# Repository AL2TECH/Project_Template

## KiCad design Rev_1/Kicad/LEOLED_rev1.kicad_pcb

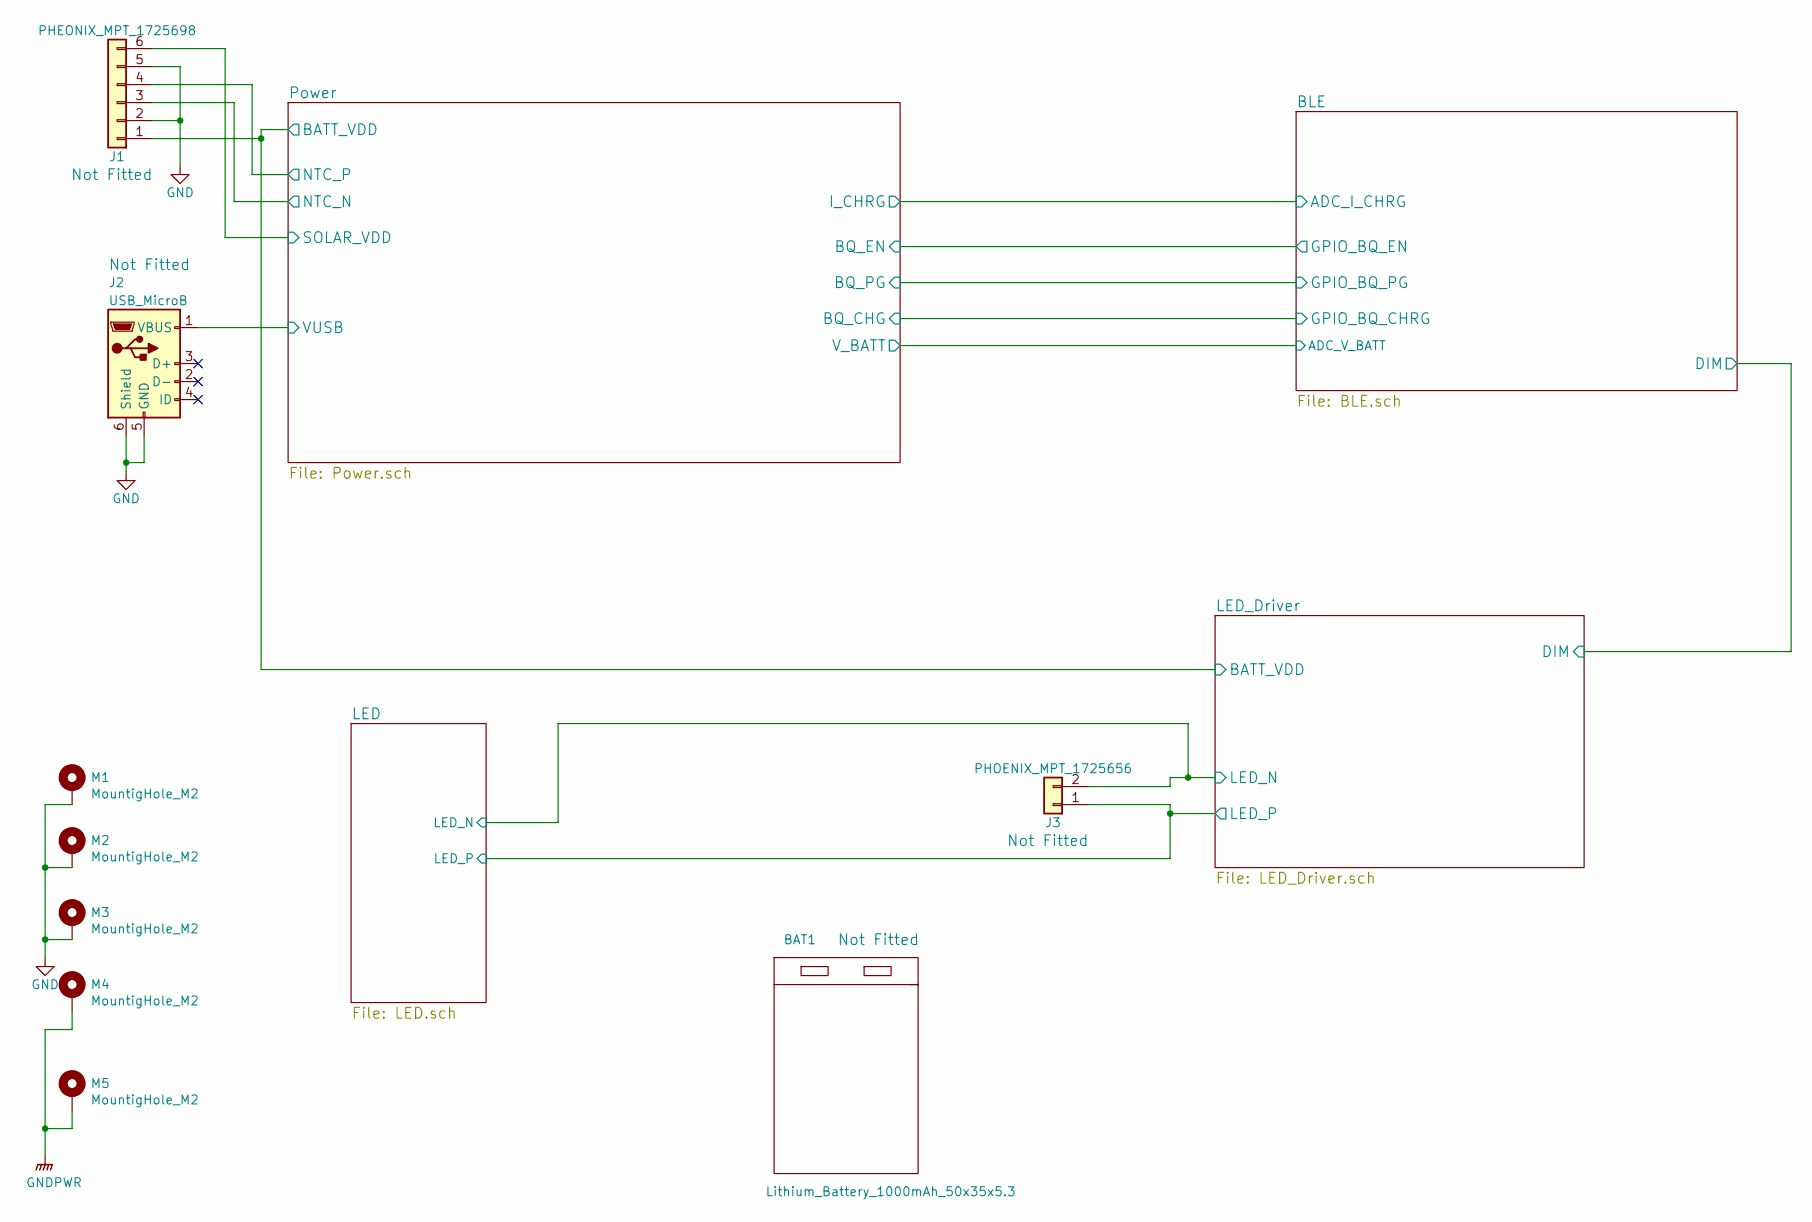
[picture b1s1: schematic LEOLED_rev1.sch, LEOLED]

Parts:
BAT1: Lithium_Battery_1000mAh_50x35x5.3; Lithium_battery_50x30x5.3; Rating 1000mAh, 3.7V; Tolerance NA; Manufacturer PN 523450
J1: PHEONIX_MPT_1725698; TerminalBlock_Pheonix_MPT-2.54mm_6pol; Rating 125V, 6A; Tolerance NA; Manufacturer PN 1725698
J2: USB_MicroB; USB_Micro-B_Molex-105017-0001; Rating NA; Tolerance NA; Manufacturer PN 1050170001
J3: PHOENIX_MPT_1725656; TerminalBlock_Pheonix_MPT-2.54mm_2pol; Rating 6A, 125V; Tolerance NA; Manufacturer PN 1725656
M1, M2, M3, M4, M5: MountigHole_M2; MountingHole_2.2mm_M2_ISO7380_Pad; Rating NA; Tolerance NA; Manufacturer PN NA

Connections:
/LED/LED_N: J3.2; also elsewhere on the board
/LED_Driver/BATT_VDD: J1.1; also elsewhere on the board
/Power/NTC_N: J1.3; also elsewhere on the board
/Power/NTC_P: J1.4; also elsewhere on the board
/Power/SOLAR_VDD: J1.6; also elsewhere on the board
/Power/VUSB: J2.1 (VBUS); also elsewhere on the board
GNDPWR: M4.1, M5.1; also elsewhere on the board

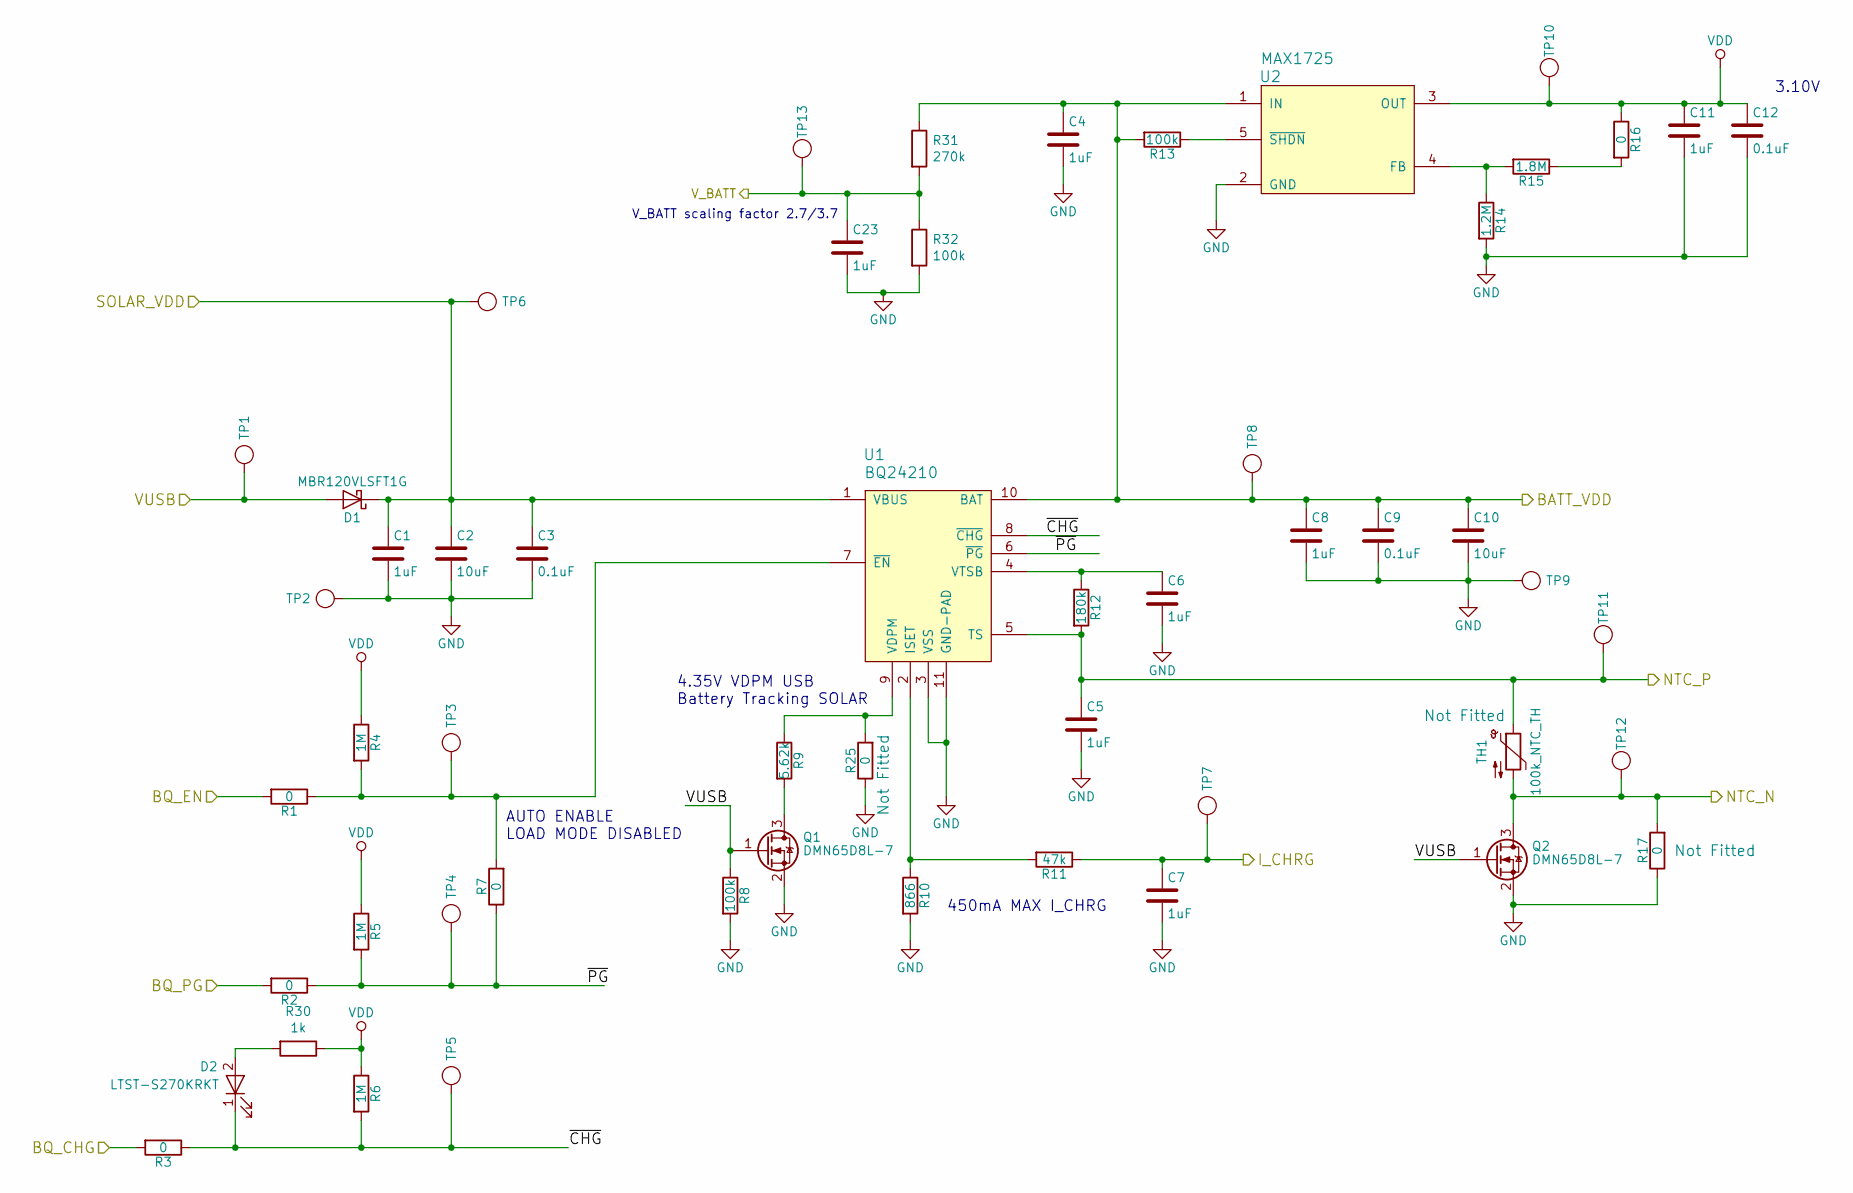
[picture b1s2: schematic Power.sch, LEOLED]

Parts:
C1, C4, C5, C6, C7, C8, C11, C23: 1uF; C_0603_1608Metric; Rating 16V; Tolerance 20% X7R; Manufacturer PN GRM188R71C105MA12D
C2, C10: 10uF; C_1206_3216Metric; Rating 16V; Tolerance 10% X7R; Manufacturer PN CL31B106KOHZW6E
C3, C9, C12: 0.1uF; C_0603_1608Metric; Rating 16V; Tolerance 10% X7R; Manufacturer PN GRM188R71C104KA01D
D1: MBR120VLSFT1G; D_SOD-123FL; Rating 20V, 1A; Tolerance NA; Manufacturer PN MBR120VLSFT1G
D2: LTST-S270KRKT; LED_0603_1608Metric_Side_Mounted; Rating 20mA; Tolerance NA; Manufacturer PN LTST-S270KRKT
Q1, Q2: DMN65D8L-7; SOT-23; Rating 60V, 310mA; Tolerance NA; Manufacturer PN DMN65D8L-7
R1, R2, R3, R7, R16, R17, R25: 0; R_0603_1608Metric; Rating 0.1W; Tolerance 1%; Manufacturer PN CRG0603ZR
R4, R5, R6: 1M; R_0603_1608Metric; Rating 0.1W; Tolerance 1%; Manufacturer PN CRG0603F1M0
R8, R13, R32: 100k; R_0603_1608Metric; Rating 0.1W; Tolerance 1%; Manufacturer PN CRG0603F100K
R9: 5.62k; R_0603_1608Metric; Rating 0.1W; Tolerance 1%; Manufacturer PN ERJ-3EKF5621V
R10: 866; R_0603_1608Metric; Rating 0.1W; Tolerance 1%; Manufacturer PN ERJ-3EKF8660V
R11: 47k; R_0603_1608Metric; Rating 0.1W; Tolerance 1%; Manufacturer PN CRCW060347K0FKEAC
R12: 180k; R_0603_1608Metric; Rating 0.1W; Tolerance 1%; Manufacturer PN CRCW0603180KFKEA
R14: 1.2M; R_0603_1608Metric; Rating 0.1W; Tolerance 1%; Manufacturer PN RC0603FR-071M2L
R15: 1.8M; R_0603_1608Metric; Rating 0.1W; Tolerance 1%; Manufacturer PN RC0603FR-071M8L
R30: 1k; R_0603_1608Metric; Rating 0.1W; Tolerance 1%; Manufacturer PN CRG0603F1K0
R31: 270k; R_0603_1608Metric; Rating 0.1W; Tolerance 1%; Manufacturer PN RC0603FR-07270KL
TH1: 100k_NTC_TH; R_0603_1608Metric; Rating NA; Tolerance 1%; Manufacturer PN NTCG164KF104FT1
TP1, TP2, TP3, TP4, TP5, TP6, TP7, TP8, TP9, TP10, TP11, TP12, TP13: Test_Point; TestPoint_Pad_D1.5mm; Rating NA; Tolerance NA; Manufacturer PN NA
U1: BQ24210; WSON-10-1EP_2x3mm_Pitch0.5mm_ThermalVias; Rating 7V; Tolerance NA; Manufacturer PN BQ24210DQCT
U2: MAX1725; SOT-23-5; Rating 12V; Tolerance NA; Manufacturer PN MAX1725EUK+T

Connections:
/BLE/ADC_I_CHRG: C7.1, R11.1, TP7.1; also elsewhere on the board
/BLE/ADC_V_BATT: C23.1, R31.2, R32.1, TP13.1; also elsewhere on the board
/LED_Driver/BATT_VDD: C4.1, C8.1, C9.1, C10.1, R13.2, R31.1, TP8.1, U1.10 (BAT), U2.1 (IN); also elsewhere on the board
/Power/BQ_CHG: R3.2; also elsewhere on the board
/Power/BQ_EN: R1.2; also elsewhere on the board
/Power/BQ_PG: R2.2; also elsewhere on the board
/Power/NTC_N: Q2.3 (D), R17.2, TH1.2, TP12.1; also elsewhere on the board
/Power/NTC_P: C5.1, R12.2, TH1.1, TP11.1, U1.5 (TS); also elsewhere on the board
/Power/SOLAR_VDD: C1.1, C2.1, C3.1, D1.1 (K), TP6.1, U1.1 (VBUS); also elsewhere on the board
/Power/VUSB: D1.2 (A), Q1.1 (G), Q2.1 (G), R8.1, TP1.1; also elsewhere on the board
/Power/~CHG: D2.1 (K), R3.1, R6.2, TP5.1, U1.8 (~CHG)
/Power/~PG: R2.1, R5.2, R7.1, TP4.1, U1.6 (~PG)
unnamed: C6.1, R12.1, U1.4 (VTSB)
unnamed: D2.2 (A), R30.2
unnamed: Q1.3 (D), R9.2
unnamed: R1.1, R4.2, R7.2, TP3.1, U1.7 (~EN)
unnamed: R10.1, R11.2, U1.2 (ISET)
unnamed: R13.1, U2.5 (~SHDN)
unnamed: R14.1, R15.2, U2.4 (FB)
unnamed: R15.1, R16.2
VDD: C11.1, C12.1, R4.1, R5.1, R6.1, R16.1, R30.1, TP10.1, U2.3 (OUT); also elsewhere on the board

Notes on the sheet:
450mA MAX I_CHRG
4.35V VDPM USB Battery Tracking SOLAR
AUTO ENABLE LOAD MODE DISABLED
3.10V
V_BATT scaling factor 2.7/3.7

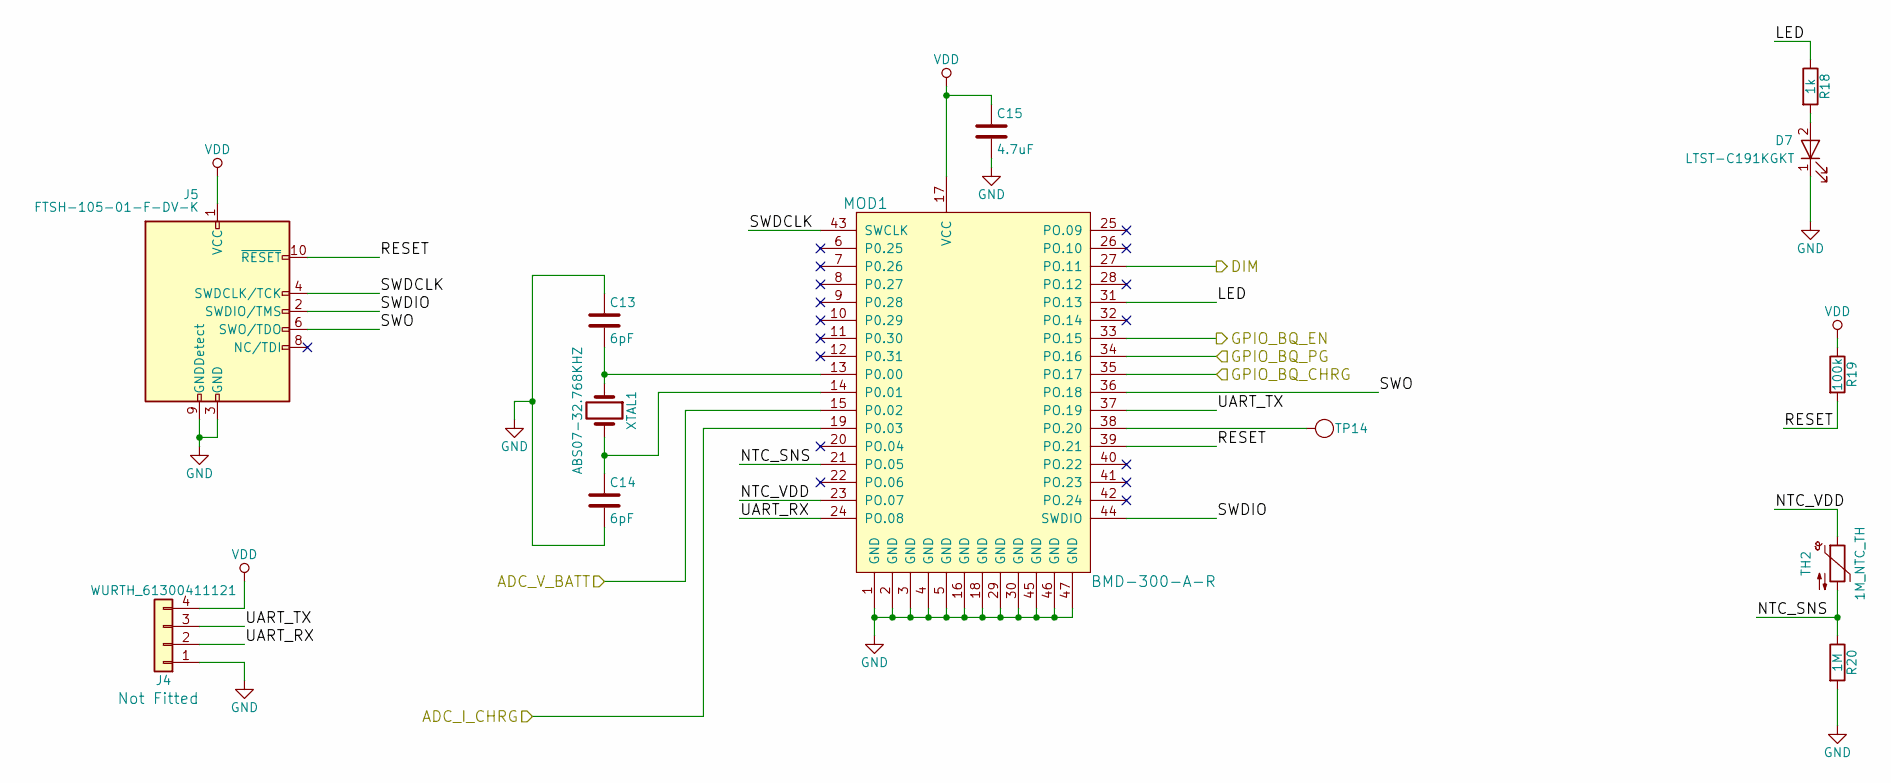
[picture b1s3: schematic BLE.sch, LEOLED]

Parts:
C13, C14: 6pF; C_0402_1005Metric; Rating 50V; Tolerance ±0.5pF; Manufacturer PN GRM1555C1H6R0DA01D
C15: 4.7uF; C_0603_1608Metric; Rating 16V; Tolerance 10% X5R; Manufacturer PN CL10A475KO8NNNC
D7: LTST-C191KGKT; LED_0603_1608Metric; Rating 20mA; Tolerance NA; Manufacturer PN LTST-C191KGKT
J4: WURTH_61300411121; Pin_Header_Straight_1x04_Pitch2.54mm; Rating NA; Tolerance NA; Manufacturer PN 61300411121
J5: FTSH-105-01-F-DV-K; Pin_Header_Straight_2x05_Pitch1.27mm_SMD; Rating NA; Tolerance NA; Manufacturer PN FTSH-105-01-F-DV-K
MOD1: BMD-300-A-R; BLE_Rigado_BMD-300; Rating 1.7V to 3V; Tolerance NA; Manufacturer PN BMD-300-A-R
R18: 1k; R_0603_1608Metric; Rating 0.1W; Tolerance 1%; Manufacturer PN CRG0603F1K0
R19: 100k; R_0603_1608Metric; Rating 0.1W; Tolerance 1%; Manufacturer PN CRG0603F100K
R20: 1M; R_0603_1608Metric; Rating 0.1W; Tolerance 1%; Manufacturer PN CRG0603F1M0
TH2: 1M_NTC_TH; R_0603_1608Metric; Rating 0.1W; Tolerance 3%, B25/50 4661K; Manufacturer PN NTCG164QH105HT1
TP14: Test_Point; TestPoint_Pad_D1.5mm; Rating NA; Tolerance NA; Manufacturer PN NA
XTAL1: ABS07-32.768KHZ; ABS07-32.768KHZ-7-T; Rating NA; Tolerance 20ppm; Manufacturer PN ABS07-32.768KHZ-7-T

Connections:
/BLE/ADC_I_CHRG: MOD1.19 (P0.03); also elsewhere on the board
/BLE/ADC_V_BATT: MOD1.15 (P0.02); also elsewhere on the board
/BLE/DIM: MOD1.27 (PO.11); also elsewhere on the board
/BLE/LED: MOD1.31 (PO.13), R18.1
/BLE/NTC_SNS: MOD1.21 (PO.05), R20.1, TH2.2
/BLE/NTC_VDD: MOD1.23 (PO.07), TH2.1
/BLE/RESET: J5.10 (~RESET~), MOD1.39 (PO.21), R19.2
/BLE/SWDCLK: J5.4 (SWDCLK/TCK), MOD1.43 (SWCLK)
/BLE/SWDIO: J5.2 (SWDIO/TMS), MOD1.44 (SWDIO)
/BLE/SWO: J5.6 (SWO/TDO), MOD1.36 (PO.18)
/BLE/UART_RX: J4.2, MOD1.24 (PO.08)
/BLE/UART_TX: J4.3, MOD1.37 (PO.19)
/Power/BQ_CHG: MOD1.35 (PO.17); also elsewhere on the board
/Power/BQ_EN: MOD1.33 (PO.15); also elsewhere on the board
/Power/BQ_PG: MOD1.34 (PO.16); also elsewhere on the board
unnamed: C13.2, MOD1.13 (P0.00), XTAL1.1
unnamed: C14.1, MOD1.14 (P0.01), XTAL1.2
unnamed: D7.2 (A), R18.2
unnamed: MOD1.38 (PO.20), TP14.1
VDD: C15.1, J4.4, J5.1 (VCC), MOD1.17 (VCC), R19.1; also elsewhere on the board

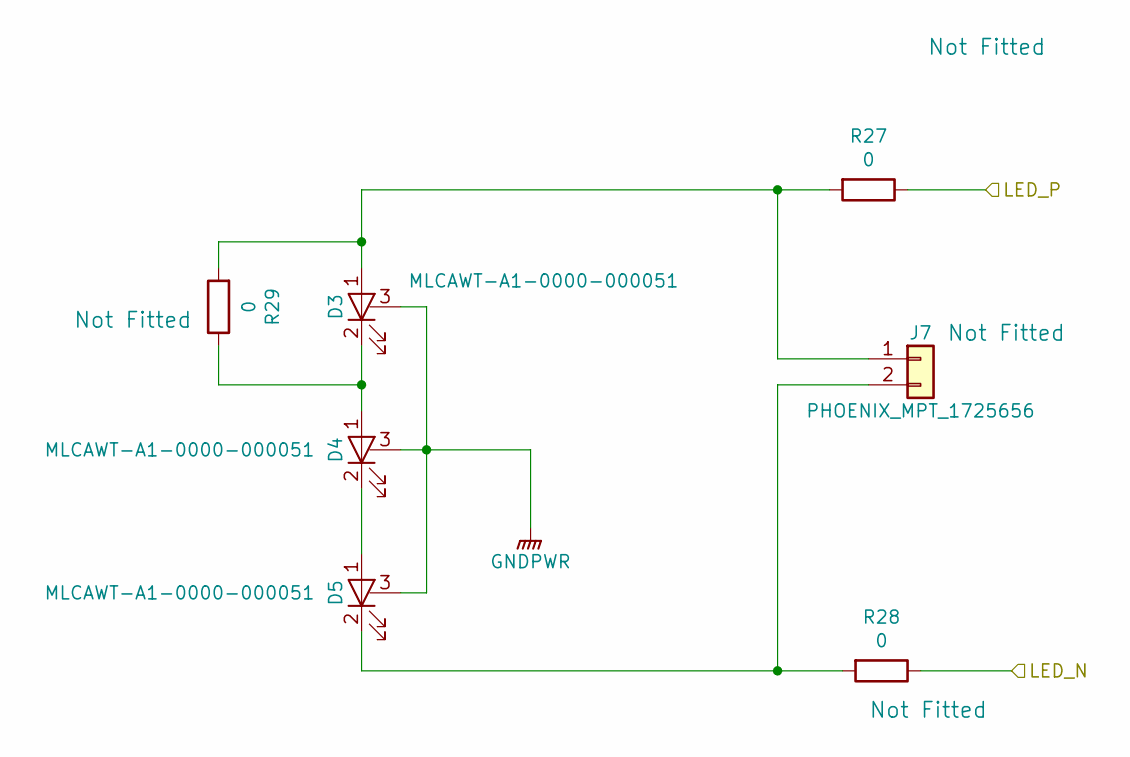
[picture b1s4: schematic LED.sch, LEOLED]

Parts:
D3, D4, D5: MLCAWT-A1-0000-000051; Cree_MLC; Rating 300mW; Tolerance NA; Manufacturer PN MLCAWT-A1-0000-000051
J7: PHOENIX_MPT_1725656; TerminalBlock_Pheonix_MPT-2.54mm_2pol; Rating 6A, 125V; Tolerance NA; Manufacturer PN 1725656
R27, R28, R29: 0; R_0805_2012Metric; Rating 0.125W; Tolerance NA; Manufacturer PN ERJ-6GEY0R00V

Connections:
/LED/LED_N: R28.1; also elsewhere on the board
GNDPWR: D3.3 (HS), D4.3 (HS), D5.3 (HS); also elsewhere on the board
unnamed: D3.1 (A), J7.1, R27.2, R29.2
unnamed: D3.2 (K), D4.1 (A), R29.1
unnamed: D4.2 (K), D5.1 (A)
unnamed: D5.2 (K), J7.2, R28.2

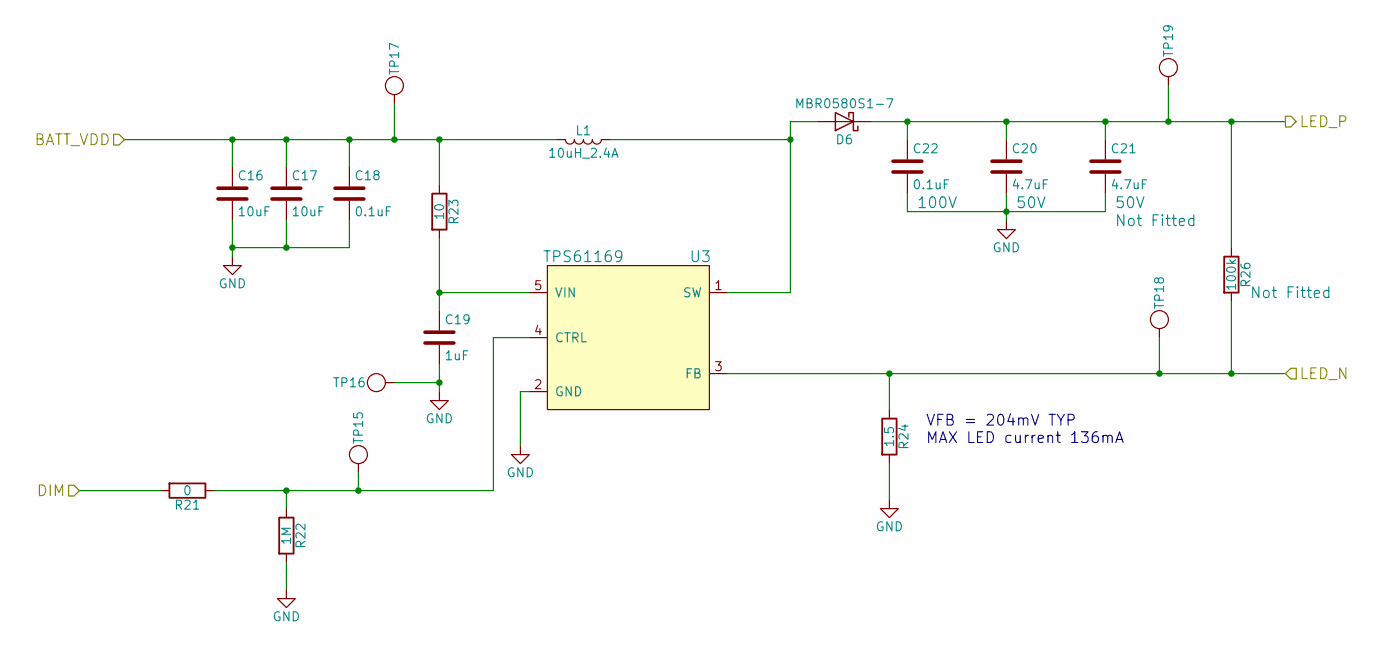
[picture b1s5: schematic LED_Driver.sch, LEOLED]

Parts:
C16, C17: 10uF; C_1206_3216Metric; Rating 16V; Tolerance 10% X7R; Manufacturer PN CL31B106KOHZW6E
C18: 0.1uF; C_0603_1608Metric; Rating 16V; Tolerance 10% X7R; Manufacturer PN GRM188R71C104KA01D
C19: 1uF; C_0603_1608Metric; Rating 16V; Tolerance 20% X7R; Manufacturer PN GRM188R71C105MA12D
C20, C21: 4.7uF; C_1206_3216Metric; Rating 50V; Tolerance X5R; Manufacturer PN CL31A475KB9LNNC
D6: MBR0580S1-7; D_SOD-123; Rating 500mA, 80V; Tolerance NA; Manufacturer PN MBR0580S1-7
L1: 10uH_2.4A; L_Wurth_5030; Rating 2.4A; Tolerance 20%; Manufacturer PN 74437336100
R21: 0; R_0603_1608Metric; Rating 0.1W; Tolerance 1%; Manufacturer PN CRG0603ZR
R22: 1M; R_0603_1608Metric; Rating 0.1W; Tolerance 1%; Manufacturer PN CRG0603F1M0
R23: 10; R_0603_1608Metric; Rating 0.1W; Tolerance 1%; Manufacturer PN AC0603FR-0710RL
R24: 1.5; R_0805_2012Metric; Rating 0.125W; Tolerance 1%; Manufacturer PN RC0805FR-071R5L
R25: 0.1uF; C_0805_2012Metric; Rating 100V; Tolerance 10%; Manufacturer PN GCM21BR72A104KA37L
R26: 100k; R_0603_1608Metric; Rating 0.1W; Tolerance 1%; Manufacturer PN CRG0603F100K
TP15, TP16, TP17, TP18, TP19: Test_Point; TestPoint_Pad_D1.5mm; Rating NA; Tolerance NA; Manufacturer PN NA
U3: TPS61169; TI_SC-70-5; Rating NA; Tolerance NA; Manufacturer PN TPS61169DCKR

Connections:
/BLE/DIM: R21.2; also elsewhere on the board
/LED/LED_N: R24.1, R26.2, TP18.1, U3.3 (FB); also elsewhere on the board
/LED_Driver/BATT_VDD: C16.1, C17.1, C18.1, L1.2, R23.1, TP17.1; also elsewhere on the board
unnamed: C19.1, R23.2, U3.5 (VIN)
unnamed: D6.2 (A), L1.1, U3.1 (SW)
unnamed: R21.1, R22.1, TP15.1, U3.4 (CTRL)

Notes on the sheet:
VFB = 204mV TYP MAX LED current 136mA

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
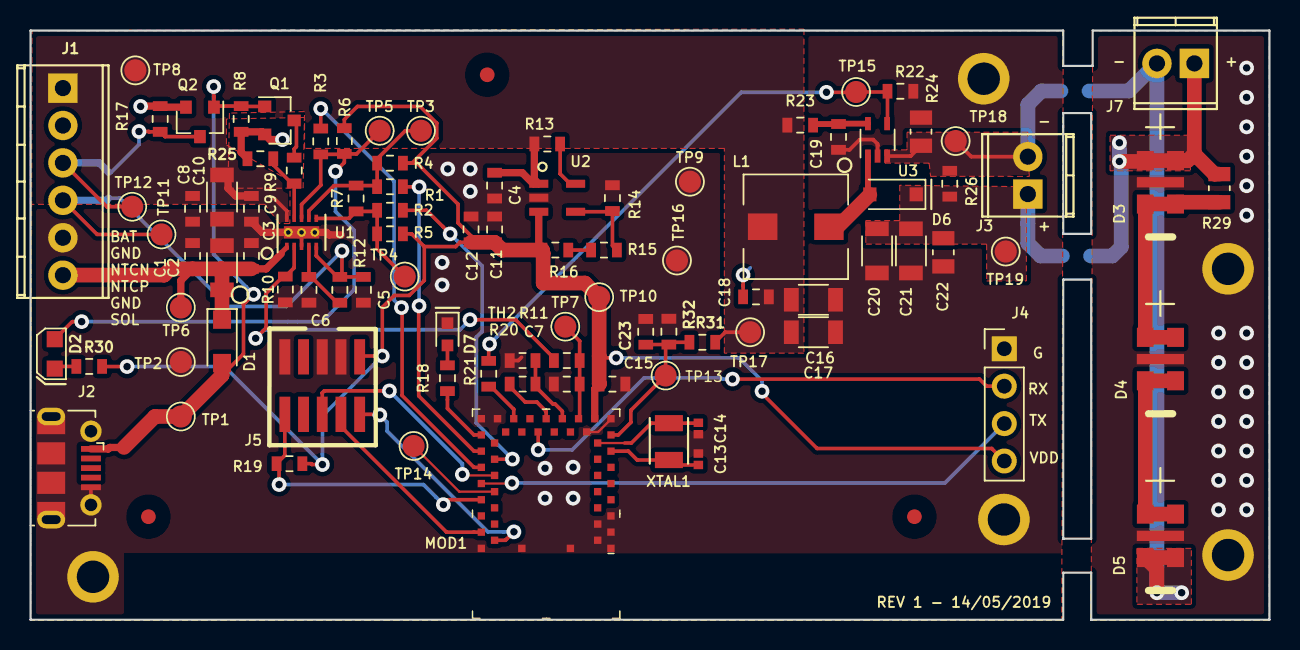
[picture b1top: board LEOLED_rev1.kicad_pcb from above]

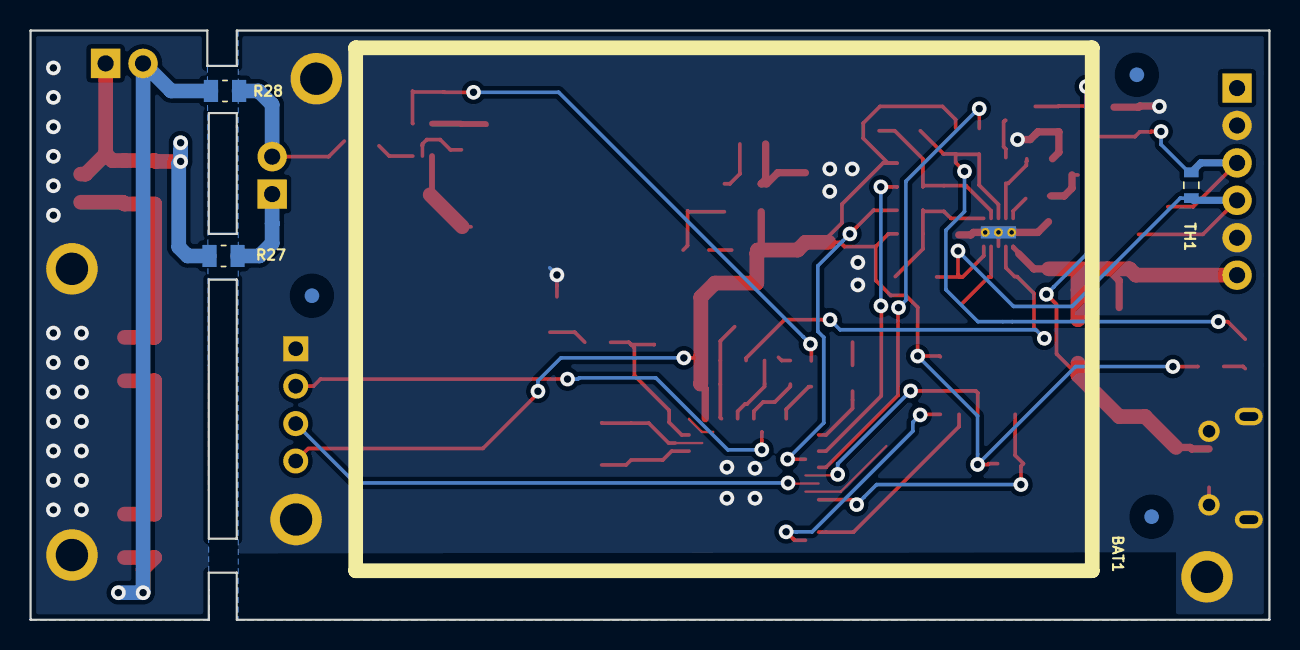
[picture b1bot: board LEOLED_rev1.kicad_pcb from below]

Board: 2 copper layers, 84.1 x 40.0 mm, 109 parts (7 on the bottom side), 47 nets.

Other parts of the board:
C22: 0.1uF; C_0805_2012Metric
FID1, FID2, FID3, FID4, FID5, FID6: Fiducial

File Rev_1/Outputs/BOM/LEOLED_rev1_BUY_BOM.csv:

,References,Description,Manufacturer,Manufacturer PN,Rating,Supplier,Supplier Link,Supplier PN,Tolerance,Value,Footprint,Quantity
1,C22,0.1µF ±10% 100V Ceramic Capacitor X7R 0805 (2012 Metric),Murata Electronics North America,GCM21BR72A104KA37L,100V,Digy-Key,https://www.digikey.com/product-detail/en/murata-electronics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,490-4789-2-ND,10%,0.1uF,C_0805_2012Metric,1
2,"C3, C9, C12, C18",0.1µF ±10% 16V Ceramic Capacitor X7R 0603 (1608 Metric),Murata Electronics North America,GRM188R71C104KA01D,16V,Digy-Key,https://www.digikey.com/product-detail/en/murata-electronics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,490-1532-1-ND,10% X7R ,0.1uF,C_0603_1608Metric,4
3,"C2, C10, C16, C17",10µF ±10% 16V Ceramic Capacitor X7R 1206 (3216 Metric),Samsung Electro-Mechanics,CL31B106KOHZW6E,16V,Digy-Key,https://www.digikey.com/product-detail/en/samsung-electro-me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,1276-7032-1-ND,10% X7R,10uF,C_1206_3216Metric,4
4,"C1, C4, C5, C6, C7, C8, C11, C19, C23",1uF ±20% 16V Ceramic Capacitor X7R 0603 (1608 Metric),Murata Electronics North America,GRM188R71C105MA12D,16V,Digy-Key,https://www.digikey.com/product-detail/en/murata-electronics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,490-6424-1-ND,20% X7R ,1uF,C_0603_1608Metric,9
5,C15,4.7µF ±10% 16V Ceramic Capacitor X5R 0603 (1608 Metric),Samsung Electro-Mechanics,CL10A475KO8NNNC,16V,Digy-Key,https://www.digikey.com/product-detail/en/samsung-electro-me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,1276-1784-1-ND,10% X5R,4.7uF,C_0603_1608Metric,1
6,C20,4.7µF ±10% 50V Ceramic Capacitor X5R 1206 (3216 Metric),Samsung Electro-Mechanics,CL31A475KB9LNNC,50V,Digy-Key,https://www.digikey.com/product-detail/en/samsung-electro-me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,1276-2731-2-ND,X5R,4.7uF,C_1206_3216Metric,1
7,"C13, C14","6pF ±0.5pF 50V Ceramic Capacitor C0G, NP0 0402",Murata Electronics North America,GRM1555C1H6R0DA01D,50V,Digy-Key,https://www.digikey.com/products/en?keywords=490-5877-1-ND,490-5877-1-ND,±0.5pF,6pF,C_0402_1005Metric,2
8,"R1, R2, R3, R7, R16, R21","0 Ohms Jumper 0.1W, 1/10W Chip Resistor 0603 (1608 Metric)",TE Connectivity Passive Product,CRG0603ZR,0.1W,Digy-Key,https://www.digikey.com/product-detail/en/te-connectivity-pa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,A106051CT-ND,1%,0,R_0603_1608Metric,6
9,"R4, R5, R6, R20, R22","1 MOhms ±1% 0.1W, 1/10W Chip Resistor 0603 (1608 Metric)",TE Connectivity,CRG0603F1M0,0.1W,Digy-Key,https://www.digikey.com/product-detail/en/te-connectivity-pa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,A121559CT-ND,1%,1M,R_0603_1608Metric,5
10,"R18, R30","1 kOhms ±1% 0.1W, 1/10W Chip Resistor 0603 (1608 Metric) Thick Film",TE Connectivity,CRG0603F1K0,0.1W,Digy-Key,https://www.digikey.com/product-detail/en/te-connectivity-pa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,A106049TR-ND,1%,1k,R_0603_1608Metric,2
11,R14,"1.2 MOhms ±1% 0.1W, 1/10W Chip Resistor 0603 (1608 Metric) Moisture Resistant Thick Film",Yageo,RC0603FR-071M2L,0.1W,Digy-Key,https://www.digikey.com/product-detail/en/yageo/RC0603FR-071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,311-1.20MHRCT-ND,1%,1.2M,R_0603_1608Metric,1
12,R24,"1.5 Ohms ±1% 0.125W, 1/8W Chip Resistor 0805 (2012 Metric) Moisture Resistant Thick Film",Yageo,RC0805FR-071R5L,0.125W,Digy-Key,https://www.digikey.com/product-detail/en/yageo/RC0805FR-071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,311-1.50CRTR-ND,1%,1.5,R_0805_2012Metric,1
13,R15,"1.8 MOhms ±1% 0.1W, 1/10W Chip Resistor 0603 (1608 Metric) Moisture Resistant Thick Film",Yageo,RC0603FR-071M8L,0.1W,Digy-Key,https://www.digikey.com/product-detail/en/yageo/RC0603FR-071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,YAG3328CT-ND,1%,1.8M,R_0603_1608Metric,1
14,R23,"10 Ohms ±1% 0.1W, 1/10W Chip Resistor 0603 (1608 Metric) Automotive AEC-Q200, Moisture Resistant Thick Film",Yageo,AC0603FR-0710RL,0.1W,Digy-Key,https://www.digikey.com/product-detail/en/yageo/AC0603FR-071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,311-10LDTR-ND,1%,10,R_0603_1608Metric,1
15,"R8, R13, R19, R32","100 kOhms ±1% 0.1W, 1/10W Chip Resistor 0603 (1608 Metric)",TE Connectivity,CRG0603F100K,0.1W,Digy-Key,https://www.digikey.com/product-detail/en/te-connectivity-pa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,A106046CT-ND,1%,100k,R_0603_1608Metric,4
16,R12,"180 kOhms ±1% 0.1W, 1/10W Chip Resistor 0603 (1608 Metric)",Vishay Dale,CRCW0603180KFKEA,0.1W,Digy-Key,https://www.digikey.com/product-detail/en/vishay-dale/CRCW06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,541-180KHTR-ND,1%,180k,R_0603_1608Metric,1
17,R31,"270 kOhms ±1% 0.1W, 1/10W Chip Resistor 0603 (1608 Metric) ",Yageo,RC0603FR-07270KL,0.1W,Digy-Key,https://www.digikey.com/product-detail/en/yageo/RC0603FR-072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,311-270KHRCT-ND,1%,270k,R_0603_1608Metric,1
18,R11,"47 kOhms ±1% 0.1W, 1/10W Chip Resistor 0603 (1608 Metric)",Vishay Dale,CRCW060347K0FKEAC,0.1W,Digy-Key,https://www.digikey.com/product-detail/en/vishay-dale/CRCW06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,541-4021-2-ND,1%,47k,R_0603_1608Metric,1
19,R9,"5.62 kOhms ±1% 0.1W, 1/10W Chip Resistor 0603 (1608 Metric)",Panasonic Electronic Components,ERJ-3EKF5621V,0.1W,Digy-Key,https://www.digikey.com/product-detail/en/panasonic-electron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,P5.62KHDKR-ND,1%,5.62k,R_0603_1608Metric,1
20,R10,"866 Ohms ±1% 0.1W, 1/10W Chip Resistor 0603 (1608 Metric)",Panasonic Electronic Components,ERJ-3EKF8660V,0.1W,Digy-Key,https://www.digikey.com/product-detail/en/panasonic-electron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,P866HCT-ND,1%,866,R_0603_1608Metric,1
21,L1,10µH Shielded Molded Inductor 2.4A 128 mOhm Max 2-SMD,Wurth Electronics Inc.,74437336100,2.4A,Digy-Key,https://www.digikey.com/product-detail/en/wurth-electronics-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,732-6170-6-ND,20%,10uH_2.4A,L_Wurth_5030,1
22,D1,Diode Schottky 20V 1A Surface Mount SOD-123FL,ON Semiconductor,MBR120VLSFT1G,"20V, 1A",Digy-Key,https://www.digikey.com/product-detail/en/on-semiconductor/M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,MBR120VLSFT1GOSCT-ND,NA,MBR120VLSFT1G,D_SOD-123FL,1
23,D6,Diode Schottky 80V 500mA Surface Mount SOD-123,Diodes Incorporated,MBR0580S1-7,"500mA, 80V",Digy-Key,https://www.digikey.com/product-detail/en/diodes-incorporate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,MBR0580S1-7DITR-ND,NA,MBR0580S1-7,D_SOD-123,1
24,D7,Green 571nm LED Indication - Discrete 2V 0603,Lite-On Inc.,LTST-C191KGKT,20mA,Digy-Key,https://www.digikey.com/product-detail/en/lite-on-inc/LTST-C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,160-1446-2-ND,NA,LTST-C191KGKT,LED_0603_1608Metric,1
25,"D3, D4, D5",High Power LEDs - White,Cree Inc,MLCAWT-A1-0000-000051,300mW,Mouser,https://www2.mouser.com/ProductDetail/Cree-Inc/MLCAWT-A1-000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,941-MLCAWTA100000051,NA,MLCAWT-A1-0000-000051,Cree_MLC,3
26,D2,Red 631nm LED Indication - Side Mounted - Discrete 2V 0603 (1608 Metric),Lite-On Inc.,LTST-S270KRKT,20mA,Digy-Key,https://www.digikey.com/product-detail/en/lite-on-inc/LTST-S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,160-1479-1-ND,NA,LTST-S270KRKT,LED_0603_1608Metric_Side_Mounted,1
27,U1,Charger IC Lithium-Ion 10-WSON (3x2),Texas Instrument,BQ24210DQCT,7V,Digy-Key,https://www.digikey.com/product-detail/en/texas-instruments/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,296-28738-1-ND,NA,BQ24210,WSON-10-1EP_2x3mm_Pitch0.5mm_ThermalVias,1
28,U3,LED Driver IC 1 Output DC DC Regulator Step-Up (Boost) PWM Dimming 1.8A (Switch) SC-70-5,Texas Instruments,TPS61169DCKR,NA,Digy-Key,https://www.digikey.com/product-detail/en/texas-instruments/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,296-40821-1-ND,NA,TPS61169,TI_SC-70-5,1
29,U2,Linear Voltage Regulator IC Positive Adjustable 1 Output 1.5 V ~ 5 V 20mA SOT-23-5,Maxim Integrated,MAX1725EUK+T,12V,Digy-Key,https://www.digikey.com/product-detail/en/maxim-integrated/M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,MAX1725EUK+TCT-ND,NA,MAX1725,SOT-23-5,1
30,XTAL1,"32.768kHz ±20ppm Crystal 7pF 70 kOhms 2-SMD, No Lead",Abracon LLC,ABS07-32.768KHZ-7-T,NA,Digy-Key,https://www.digikey.com/products/en?keywords=535-9543-1-ND,535-9543-1-ND,20ppm,ABS07-32.768KHZ,ABS07-32.768KHZ-7-T,1
31,MOD1,MOD BLE 4.2 NORDIC NRF52832 SOC,Rigado Inc,BMD-300-A-R,1.7V to 3V,Digy-Key,https://www.digikey.com/product-detail/en/rigado-inc/BMD-300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,1604-1006-1-ND,NA,BMD-300-A-R,BLE_Rigado_BMD-300,1
32,"Q1, Q2",N-Channel 60V 310mA (Ta) 370mW (Ta) Surface Mount SOT-23,Diodes Incorporated,DMN65D8L-7,"60V, 310mA",Digy-Key,https://www.digikey.com/product-detail/en/diodes-incorporate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,DMN65D8L-7DICT-ND,NA,DMN65D8L-7,SOT-23,2
33,TH2,NTC Thermistor 1M 0603 (1608 Metric),TDK Corporation,NTCG164QH105HT1,0.1W,Digy-Key,https://www.digikey.com/product-detail/en/tdk-corporation/NT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,445-174918-1-ND,"3%, B25/50 4661K",1M_NTC_TH,R_0603_1608Metric,1
34,J5,"10 Positions Header, Cuttable Connector 0.050 (1.27mm) Surface Mount Gold",Samtec Inc.,FTSH-105-01-F-DV-K,NA,Digy-Key,https://www.digikey.com/product-detail/en/samtec-inc/FTSH-10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,SAM8796-ND,NA,FTSH-105-01-F-DV-K,Pin_Header_Straight_2x05_Pitch1.27mm_SMD,1
,,,,,,,,,,,TOT,65

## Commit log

2019-05-30 initial release
